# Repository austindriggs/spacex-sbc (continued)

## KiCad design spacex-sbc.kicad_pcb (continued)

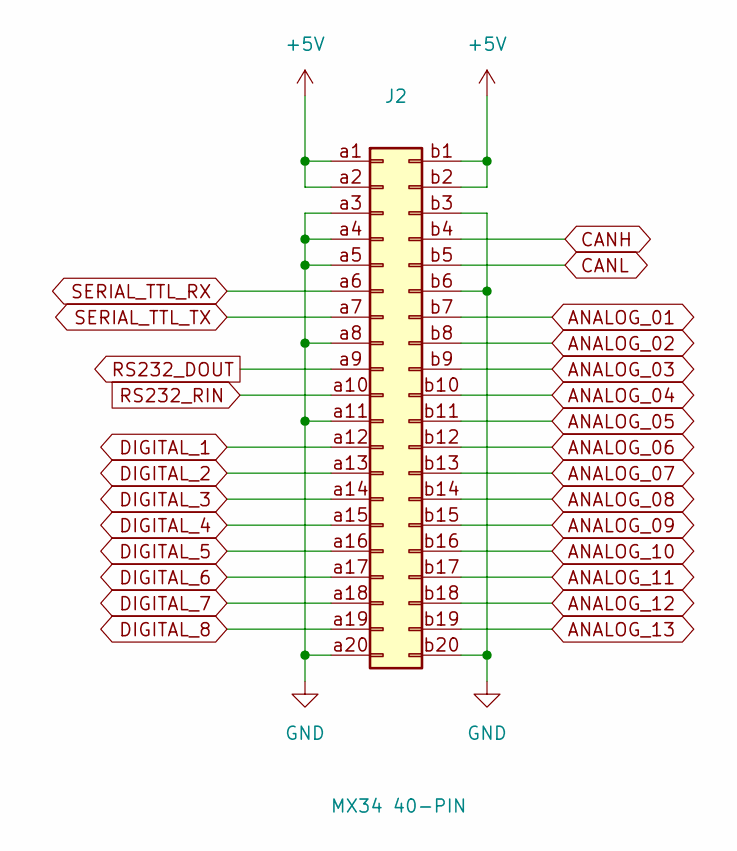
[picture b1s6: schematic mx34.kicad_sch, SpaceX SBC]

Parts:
J2: MX34 40-PIN; JAE_LY20-40P-DLT1_2x20_P2.00mm_Horizontal

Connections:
+5V: J2.a1, J2.a2, J2.b1, J2.b2; also elsewhere on the board
ANALOG_01: J2.b7; also elsewhere on the board
ANALOG_02: J2.b8; also elsewhere on the board
ANALOG_03: J2.b9; also elsewhere on the board
ANALOG_04: J2.b10; also elsewhere on the board
ANALOG_05: J2.b11; also elsewhere on the board
ANALOG_06: J2.b12; also elsewhere on the board
ANALOG_07: J2.b13; also elsewhere on the board
ANALOG_08: J2.b14; also elsewhere on the board
ANALOG_09: J2.b15; also elsewhere on the board
ANALOG_10: J2.b16; also elsewhere on the board
ANALOG_11: J2.b17; also elsewhere on the board
ANALOG_12: J2.b18; also elsewhere on the board
ANALOG_13: J2.b19; also elsewhere on the board
CANH: J2.b4; also elsewhere on the board
CANL: J2.b5; also elsewhere on the board
DIGITAL_1: J2.a12; also elsewhere on the board
DIGITAL_2: J2.a13; also elsewhere on the board
DIGITAL_3: J2.a14; also elsewhere on the board
DIGITAL_4: J2.a15; also elsewhere on the board
DIGITAL_5: J2.a16; also elsewhere on the board
DIGITAL_6: J2.a17; also elsewhere on the board
DIGITAL_7: J2.a18; also elsewhere on the board
DIGITAL_8: J2.a19; also elsewhere on the board
GND: J2.a3, J2.a4, J2.a5, J2.a8, J2.a11, J2.a20, J2.b3, J2.b6, J2.b20; also elsewhere on the board
RS232_DOUT: J2.a9; also elsewhere on the board
RS232_RIN: J2.a10; also elsewhere on the board
SERIAL_TTL_RX: J2.a6; also elsewhere on the board
SERIAL_TTL_TX: J2.a7; also elsewhere on the board

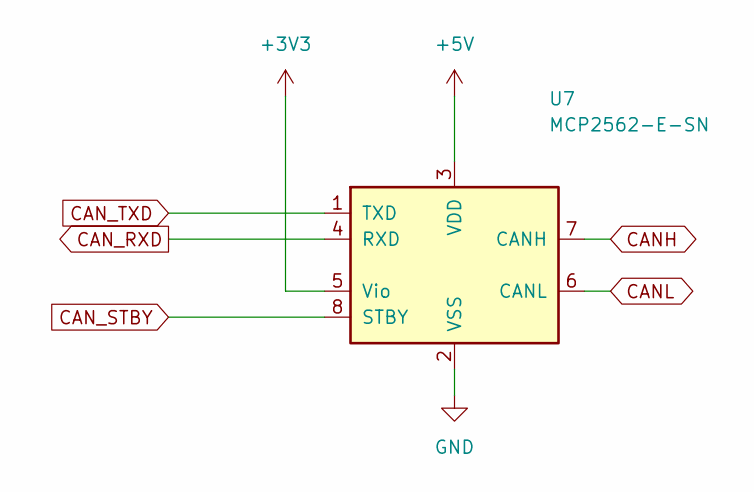
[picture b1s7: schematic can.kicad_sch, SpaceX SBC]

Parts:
U7: MCP2562-E-SN; SOIC-8_3.9x4.9mm_P1.27mm

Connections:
+3V3: U7.5 (Vio); also elsewhere on the board
+5V: U7.3 (VDD); also elsewhere on the board
CANH: U7.7 (CANH); also elsewhere on the board
CANL: U7.6 (CANL); also elsewhere on the board
CAN_RXD: U7.4 (RXD); also elsewhere on the board
CAN_STBY: U7.8 (STBY); also elsewhere on the board
CAN_TXD: U7.1 (TXD); also elsewhere on the board
GND: U7.2 (VSS); also elsewhere on the board

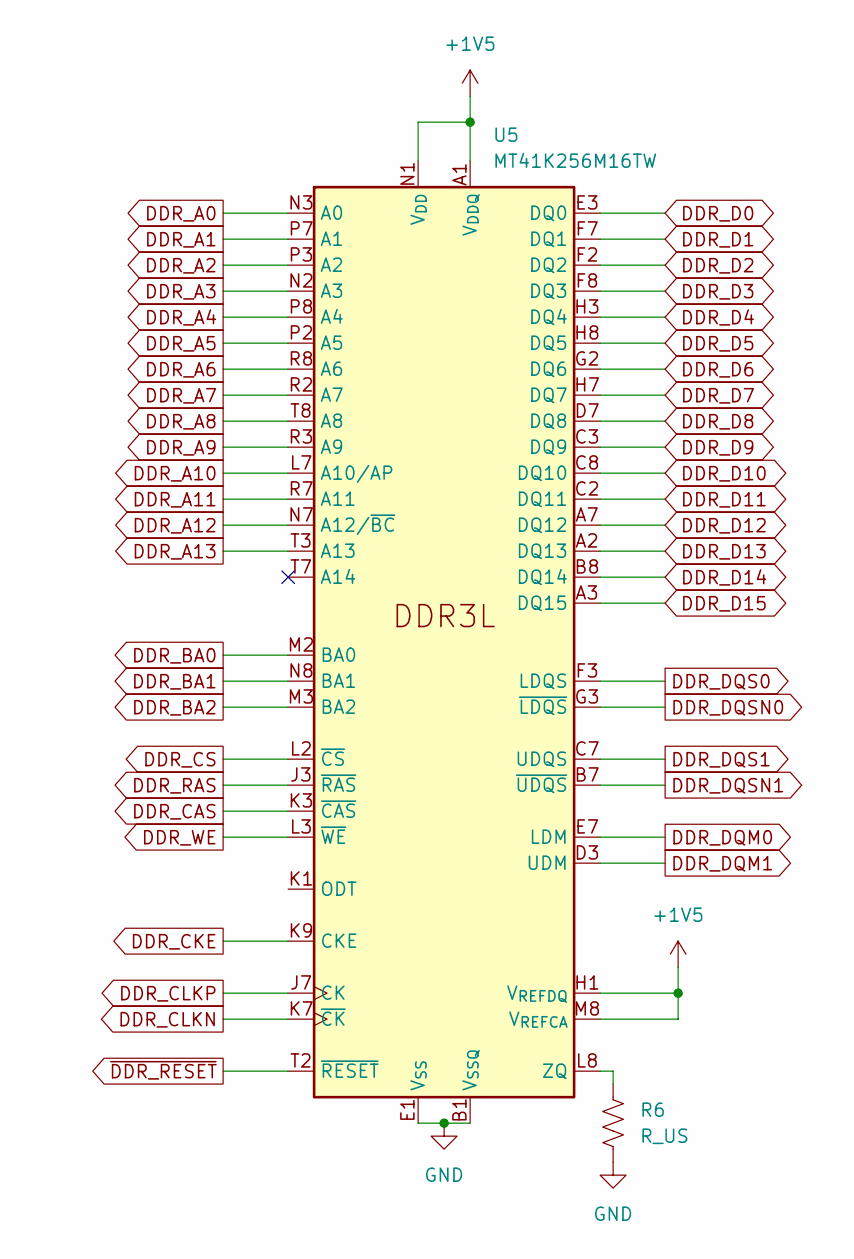
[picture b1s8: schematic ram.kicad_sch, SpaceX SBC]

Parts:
R6: R_US; R_0402_1005Metric
U5: MT41K256M16TW; Micron_FBGA-96_8x14mm_Layout9x16_P0.8mm

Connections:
+1V5: U5.A1 (V_{DDQ}), U5.A8 (V_{DDQ}), U5.B2 (V_{DD}), U5.C1 (V_{DDQ}), U5.C9 (V_{DDQ}), U5.D2 (V_{DDQ}), U5.D9 (V_{DD}), U5.E9 (V_{DDQ}), U5.F1 (V_{DDQ}), U5.G7 (V_{DD}), U5.H1 (V_{REFDQ}), U5.H2 (V_{DDQ}), U5.H9 (V_{DDQ}), U5.K2 (V_{DD}), U5.K8 (V_{DD}), U5.M8 (V_{REFCA}), U5.N1 (V_{DD}), U5.N9 (V_{DD}), U5.R1 (V_{DD}), U5.R9 (V_{DD}); also elsewhere on the board
DDR_A0: U5.N3 (A0); also elsewhere on the board
DDR_A1: U5.P7 (A1); also elsewhere on the board
DDR_A2: U5.P3 (A2); also elsewhere on the board
DDR_A3: U5.N2 (A3); also elsewhere on the board
DDR_A4: U5.P8 (A4); also elsewhere on the board
DDR_A5: U5.P2 (A5); also elsewhere on the board
DDR_A6: U5.R8 (A6); also elsewhere on the board
DDR_A7: U5.R2 (A7); also elsewhere on the board
DDR_A8: U5.T8 (A8); also elsewhere on the board
DDR_A9: U5.R3 (A9); also elsewhere on the board
DDR_A10: U5.L7 (A10/AP); also elsewhere on the board
DDR_A11: U5.R7 (A11); also elsewhere on the board
DDR_A12: U5.N7 (A12/~BC); also elsewhere on the board
DDR_A13: U5.T3 (A13); also elsewhere on the board
DDR_BA0: U5.M2 (BA0); also elsewhere on the board
DDR_BA1: U5.N8 (BA1); also elsewhere on the board
DDR_BA2: U5.M3 (BA2); also elsewhere on the board
DDR_CAS: U5.K3 (~CAS); also elsewhere on the board
DDR_CKE: U5.K9 (CKE); also elsewhere on the board
DDR_CLKN: U5.K7 (~CK); also elsewhere on the board
DDR_CLKP: U5.J7 (CK); also elsewhere on the board
DDR_CS: U5.L2 (~CS); also elsewhere on the board
DDR_D0: U5.E3 (DQ0); also elsewhere on the board
DDR_D1: U5.F7 (DQ1); also elsewhere on the board
DDR_D2: U5.F2 (DQ2); also elsewhere on the board
DDR_D3: U5.F8 (DQ3); also elsewhere on the board
DDR_D4: U5.H3 (DQ4); also elsewhere on the board
DDR_D5: U5.H8 (DQ5); also elsewhere on the board
DDR_D6: U5.G2 (DQ6); also elsewhere on the board
DDR_D7: U5.H7 (DQ7); also elsewhere on the board
DDR_D8: U5.D7 (DQ8); also elsewhere on the board
DDR_D9: U5.C3 (DQ9); also elsewhere on the board
DDR_D10: U5.C8 (DQ10); also elsewhere on the board
DDR_D11: U5.C2 (DQ11); also elsewhere on the board
DDR_D12: U5.A7 (DQ12); also elsewhere on the board
DDR_D13: U5.A2 (DQ13); also elsewhere on the board
DDR_D14: U5.B8 (DQ14); also elsewhere on the board
DDR_D15: U5.A3 (DQ15); also elsewhere on the board
DDR_DQM0: U5.E7 (LDM); also elsewhere on the board
DDR_DQM1: U5.D3 (UDM); also elsewhere on the board
DDR_DQS0: U5.F3 (LDQS); also elsewhere on the board
DDR_DQS1: U5.C7 (UDQS); also elsewhere on the board
DDR_DQSN0: U5.G3 (~LDQS); also elsewhere on the board
DDR_DQSN1: U5.B7 (~UDQS); also elsewhere on the board
DDR_RAS: U5.J3 (~RAS); also elsewhere on the board
DDR_WE: U5.L3 (~WE); also elsewhere on the board
GND: R6.2, U5.A9 (V_{SS}), U5.B1 (V_{SSQ}), U5.B3 (V_{SS}), U5.B9 (V_{SSQ}), U5.D1 (V_{SSQ}), U5.D8 (V_{SSQ}), U5.E1 (V_{SS}), U5.E2 (V_{SSQ}), U5.E8 (V_{SSQ}), U5.F9 (V_{SSQ}), U5.G1 (V_{SSQ}), U5.G8 (V_{SS}), U5.G9 (V_{SSQ}), U5.J2 (V_{SS}), U5.J8 (V_{SS}), U5.M1 (V_{SS}), U5.M9 (V_{SS}), U5.P1 (V_{SS}), U5.P9 (V_{SS}), U5.T1 (V_{SS}), U5.T9 (V_{SS}); also elsewhere on the board
unnamed: R6.1, U5.L8 (ZQ)
~DDR_RESET: U5.T2 (~RESET); also elsewhere on the board

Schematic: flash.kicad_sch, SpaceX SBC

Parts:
U8: 28F400; BGA-63_9x11mm_Layout10x12_P0.8mm; not fitted
U11: MT40A512M16JY; BGA-63_9x11mm_Layout10x12_P0.8mm

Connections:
+1V8: U8.1 (VPP), U8.23 (VCC), U11.A1 (V_{DDQ}), U11.A9 (V_{DDQ}), U11.B1 (V_{PP}), U11.B3 (V_{DD}), U11.B9 (V_{DD}), U11.C1 (V_{DDQ}), U11.D1 (V_{DD}), U11.D9 (V_{DDQ}), U11.F2 (V_{DDQ}), U11.F8 (V_{DDQ}), U11.G1 (V_{DDQ}), U11.G7 (V_{DD}), U11.G9 (V_{DDQ}), U11.J1 (V_{DD}), U11.J2 (V_{DDQ}), U11.J8 (V_{DDQ}), U11.J9 (V_{DD}), U11.L1 (V_{DD}), U11.L9 (V_{DD}), U11.R1 (V_{DD}), U11.R9 (V_{PP}), U11.T9 (V_{DD})
FLASH_BYTE: U8.12 (CE), U8.33 (BYTE), U11.A3 (DQ8), U11.B7 (UDQS_t), U11.C2 (DQ12), U11.C8 (DQ13), U11.E2 (NF/~UDM/~UDBI), U11.F3 (LDQS_c), U11.K2 (CKE), U11.L3 (~ACT), U11.L8 (A16/~RAS), U11.M7 (A12/~BC), U11.N9 (TEN), U11.P1 (~RESET), U11.R2 (A8); also elsewhere on the board
FLASH_D1: U8.17 (D1), U11.F7 (DQ1); also elsewhere on the board
FLASH_D2: U8.19 (D2), U11.H3 (DQ2); also elsewhere on the board
FLASH_D3: U8.21 (D3), U11.H7 (DQ3); also elsewhere on the board
FLASH_D5: U8.26 (D5), U11.H8 (DQ5); also elsewhere on the board
FLASH_D6: U8.28 (D6), U11.J3 (DQ6); also elsewhere on the board
FLASH_D7: U8.30 (D7), U11.J7 (DQ7); also elsewhere on the board
FLASH_OE: U8.14 (OE), U11.A7 (UDQS_c), U11.C7 (DQ11), U11.G3 (LDQS_t), U11.L7 (~CS), U11.R7 (A9), U11.T8 (A13); also elsewhere on the board
FLASH_PR: U8.44 (PR), U11.B8 (DQ9), U11.D3 (DQ14), U11.E7 (NF/~LDM/~LDBI), U11.K3 (ODT), U11.K8 (CK_c), U11.M8 (A15/~CAS), U11.T2 (A11); also elsewhere on the board
FLASH_WE: U8.43 (WE), U11.C3 (DQ10), U11.D7 (DQ15), U11.K7 (CK_t), U11.L2 (A14/~WE), U11.M3 (A10/AP), U11.T3 (PAR); also elsewhere on the board
GND: U8.13 (GND), U8.32 (GND), U11.A2 (V_{SSQ}), U11.A8 (V_{SSQ}), U11.B2 (V_{SS}), U11.C9 (V_{SSQ}), U11.D2 (V_{SSQ}), U11.D8 (V_{SSQ}), U11.E1 (V_{SS}), U11.E3 (V_{SSQ}), U11.E8 (V_{SSQ}), U11.E9 (V_{SS}), U11.F1 (V_{SSQ}), U11.G8 (V_{SS}), U11.H1 (V_{SSQ}), U11.H9 (V_{SSQ}), U11.K1 (V_{SS}), U11.K9 (V_{SS}), U11.M9 (V_{SS}), U11.N1 (V_{SS}), U11.T1 (V_{SS}); also elsewhere on the board
unnamed: U8.15 (D0), U11.G2 (DQ0)
unnamed: U8.24 (D4), U11.H2 (DQ4)

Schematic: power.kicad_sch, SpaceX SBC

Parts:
C7, C8, C11, C12: C; C_1206_3216Metric
C9, C13: C; C_0402_1005Metric
C10, C16: C_Polarized; CP_Elec_5x3
D1, D2: D_Schottky; D_0603_1608Metric
J3: Conn_01x02; Molex_Micro-Fit_3.0_43650-0200_1x02_P3.00mm_Horizontal
L1, L2: L_Iron; L_6.3x6.3_H3
R1, R2, R3, R4: R_US; R_0402_1005Metric
U6, U9: TPS5430DDA; TI_SO-PowerPAD-8_ThermalVias
U10: MCP16501TE-E/RMB; QFN-24-1EP_4x4mm_P0.5mm_EP2.7x2.7mm

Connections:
+3V3: C16.1, L2.2, R3.1; also elsewhere on the board
+5V: C10.1, L1.2, R1.1; also elsewhere on the board
GND: C7.2, C8.2, C10.2, C11.2, C12.2, C16.2, D1.2 (A), D2.2 (A), J3.2, R2.2, R4.2, U6.6 (GND), U6.9 (GNDPAD), U9.6 (GND), U9.9 (GNDPAD); also elsewhere on the board
unnamed: C9.2, D1.1 (K), L1.1, U6.8 (PH)
unnamed: C13.2, D2.1 (K), L2.1, U9.8 (PH)
unnamed: C9.1, U6.1 (BOOT)
unnamed: R1.2, R2.1, U6.4 (VSENSE)
unnamed: C13.1, U9.1 (BOOT)
unnamed: R3.2, R4.1, U9.4 (VSENSE)
VDC: C7.1, C8.1, C11.1, C12.1, J3.1, U6.7 (VIN), U9.7 (VIN)

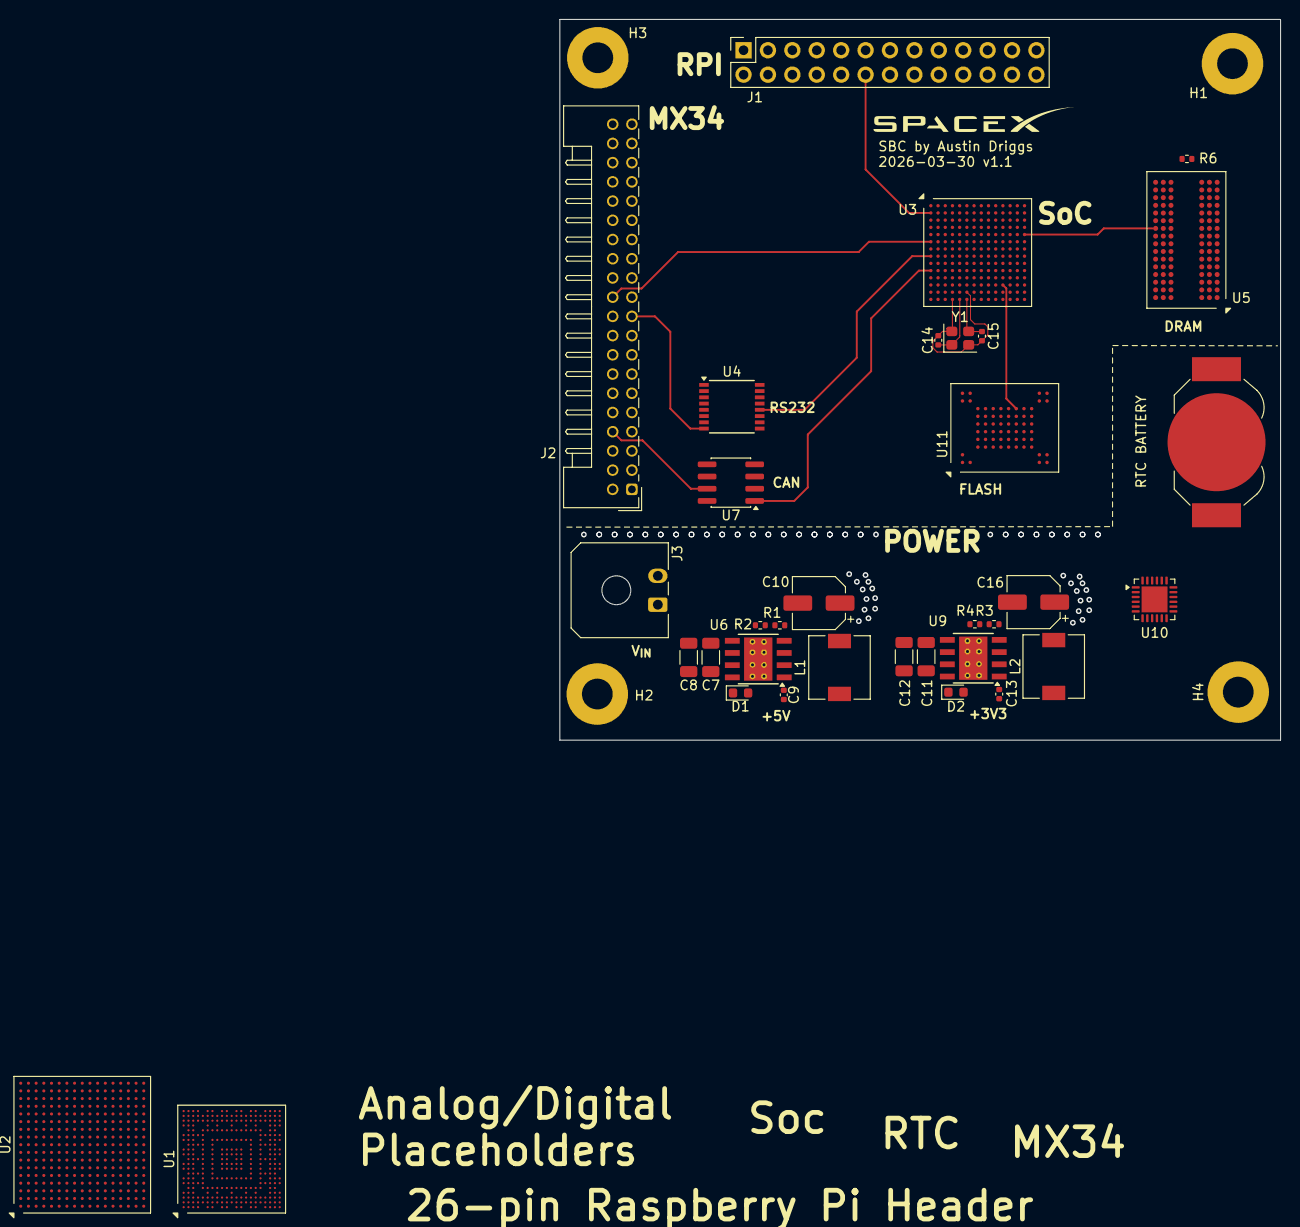
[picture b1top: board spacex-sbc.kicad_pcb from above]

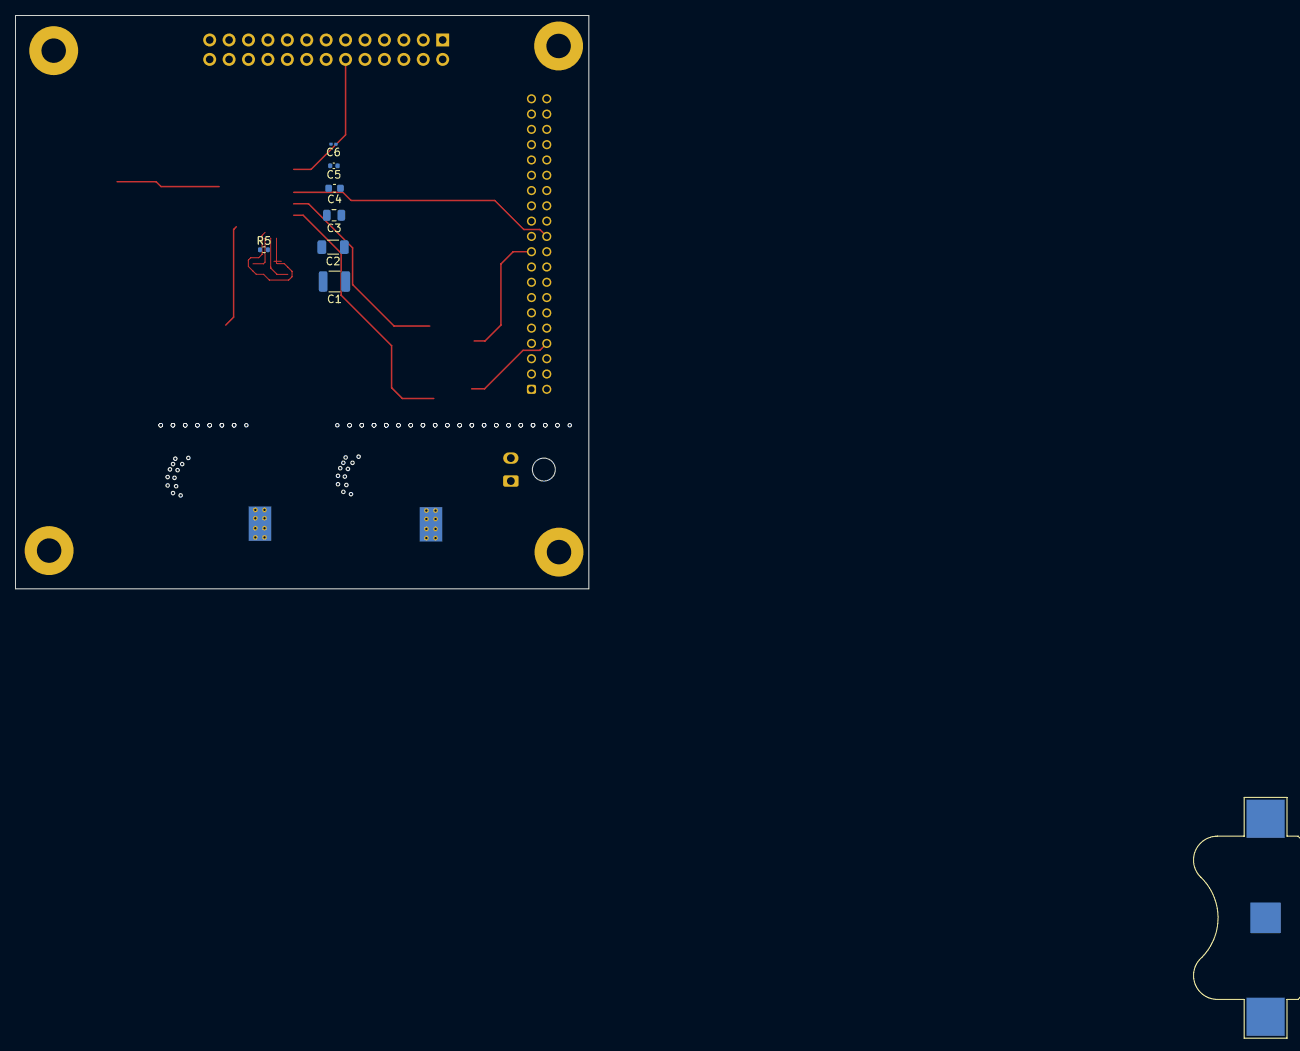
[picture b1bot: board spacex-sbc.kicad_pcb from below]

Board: 8 copper layers, 75.0 x 75.0 mm, 45 parts (7 on the bottom side), 134 nets.

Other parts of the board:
RTC BATTERY: BatteryHolder_LINX_BAT-HLD-012-SMT

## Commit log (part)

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2026-03-31 init
2026-03-31 saved
2026-04-01 mostly mocked up
2026-04-01 morning
2026-04-02 pc night
2026-04-02 backups from laptop
2026-04-02 laptop morning
2026-04-02 before caleb
2026-04-02 after caleb
2026-04-03 after rough draft submission
2026-05-08 some backups from my laptop on 2026-04-08
